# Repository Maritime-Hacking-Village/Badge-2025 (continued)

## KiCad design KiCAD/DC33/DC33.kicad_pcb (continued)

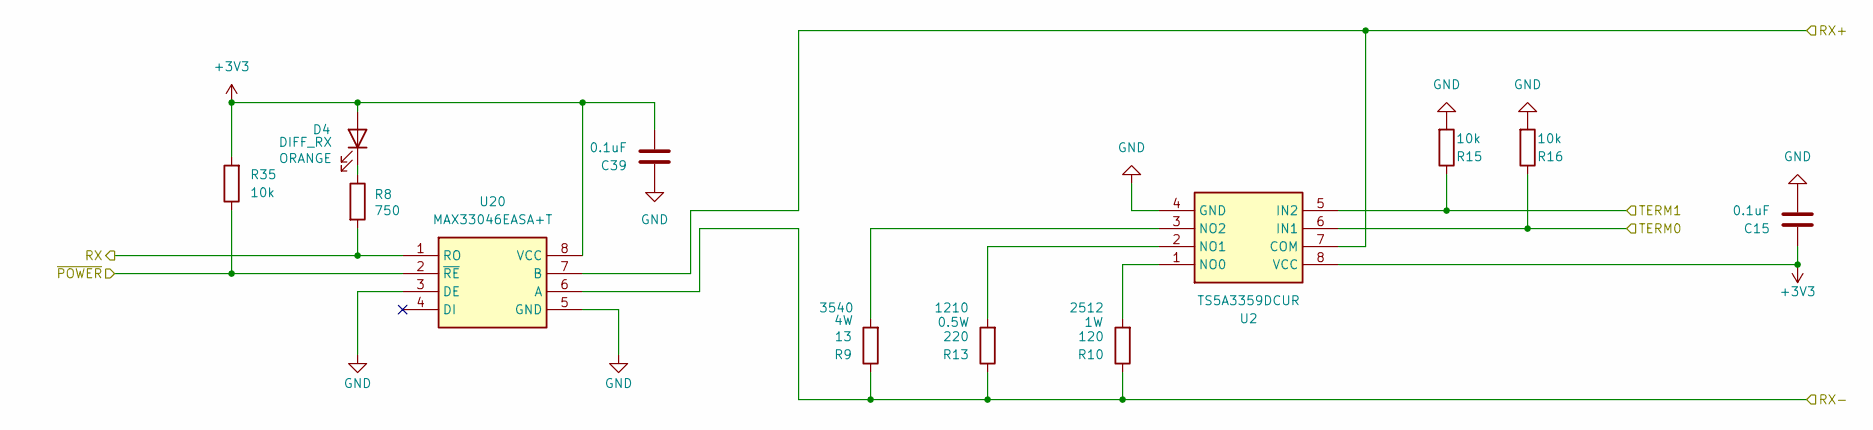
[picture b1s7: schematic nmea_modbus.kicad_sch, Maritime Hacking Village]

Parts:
C15, C39: 0.1uF; C_0603_1608Metric; Manufacturer Part Number KGM15BR71E104KT
D4: 1.8V/2MA ORANGE; LED_0603_1608Metric; Manufacturer Part Number APT1608LSECK/J4-PRV
R8: 750; R_0603_1608Metric; Tolerance 1%; Manufacturer Part Number ERJ-3EKF7500V
R9: 13; RES_3540; Tolerance 1%; Manufacturer Part Number 354013RFT
R10: 120; R_2512_6332Metric; Tolerance 1%; Manufacturer Part Number RC2512FK-07120RL
R13: 220; R_1210_3225Metric; Tolerance 1%; Manufacturer Part Number RC1210FR-07220RL
R15, R16, R35: 10k; R_0603_1608Metric; Tolerance 1%; Manufacturer Part Number CRG0603F10K
U2: TS5A3359DCUR; SOP50P310X90-8N; Manufacturer Part Number TS5A3359DCUR
U20: MAX33046EASA+T; SOIC127P600X175-8N; Manufacturer Part Number MAX33046EASA+T

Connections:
+3V3: C15.1, C39.2, D4.2 (A), R35.2, U2.8 (VCC), U20.8 (VCC); also elsewhere on the board
/Diff receiver/RX+: U2.7 (COM), U20.7 (B); also elsewhere on the board
/Diff receiver/RX-: R9.1, R10.1, R13.1, U20.6 (A); also elsewhere on the board
/PWR_RECEIVER: R35.1, U20.2 (~RE); also elsewhere on the board
/RX_TERM_SEL0: R16.1, U2.6 (IN1); also elsewhere on the board
/RX_TERM_SEL1: R15.1, U2.5 (IN2); also elsewhere on the board
/UART1_RX: R8.2, U20.1 (RO); also elsewhere on the board
GND: C15.2, C39.1, R15.2, R16.2, U2.4 (GND), U20.3 (DE), U20.5 (GND); also elsewhere on the board
unnamed: D4.1 (K), R8.1
unnamed: R10.2, U2.1 (NO0)
unnamed: R13.2, U2.2 (NO1)
unnamed: R9.2, U2.3 (NO2)

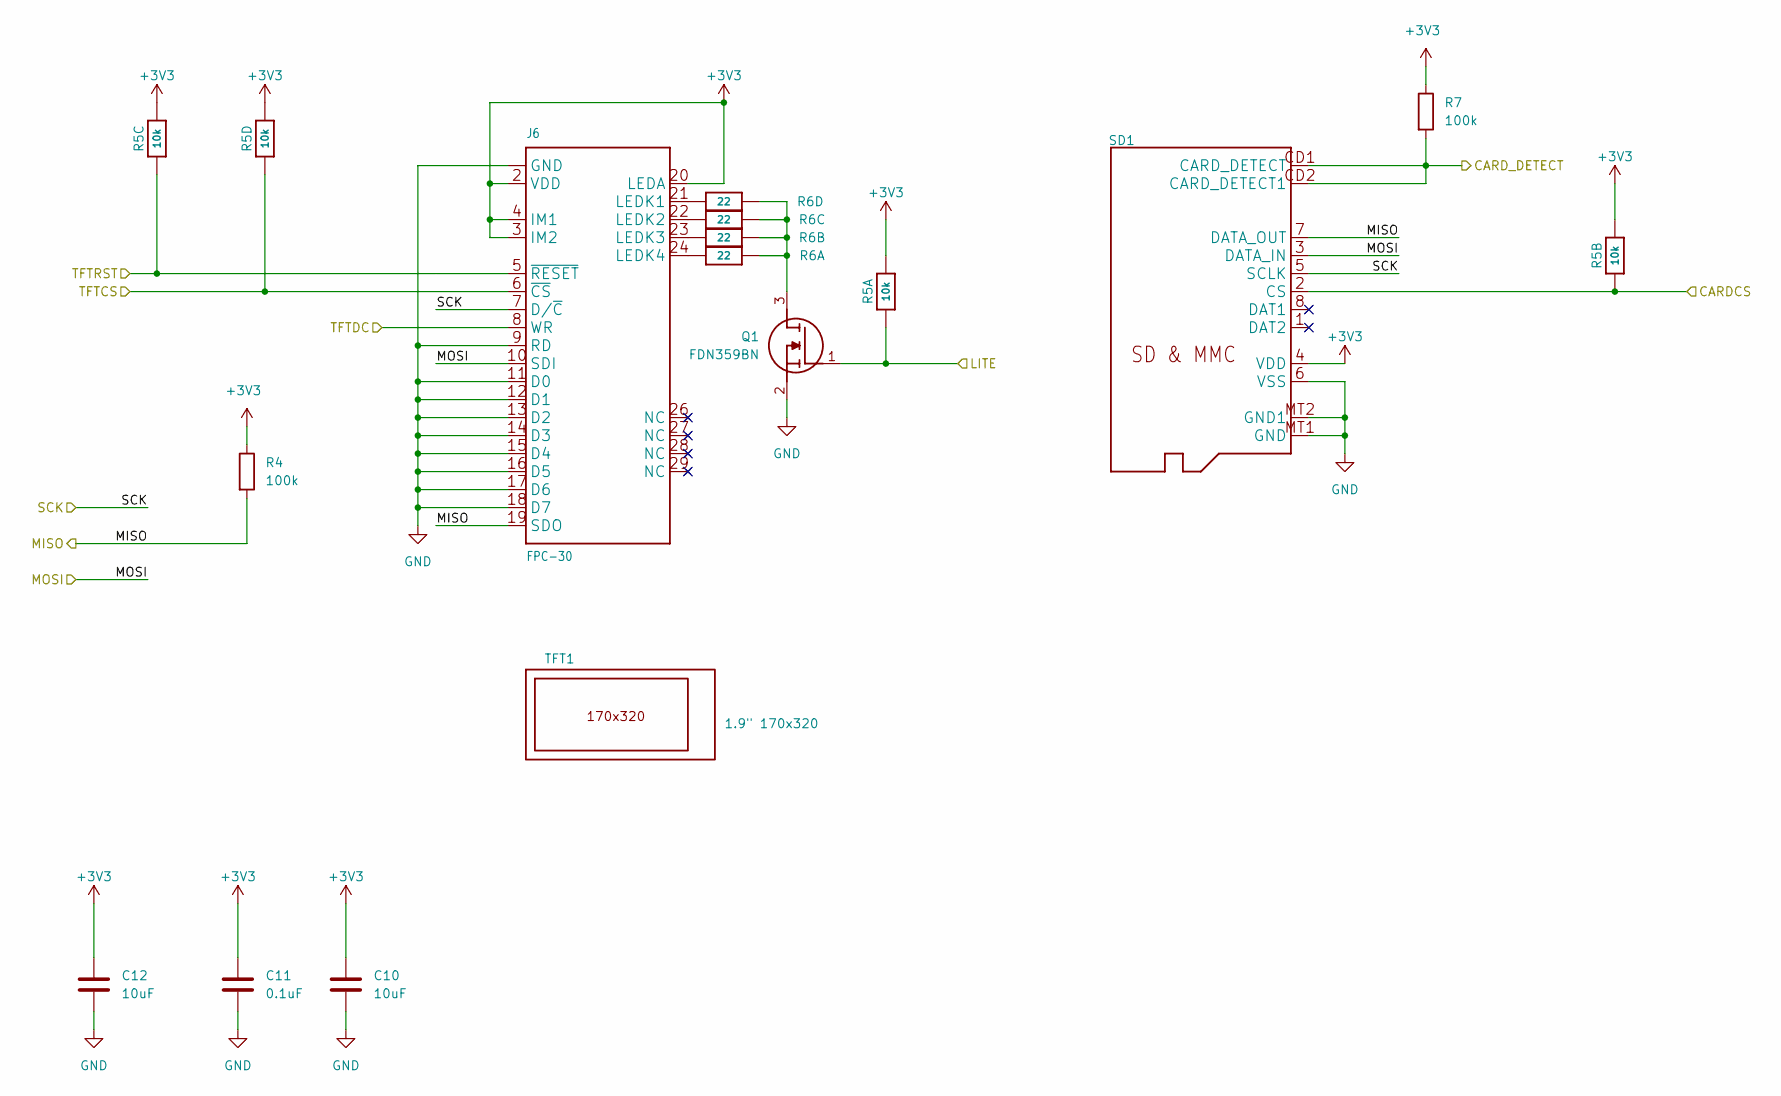
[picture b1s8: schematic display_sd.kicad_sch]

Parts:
C10, C12: 10uF; C_0603_1608Metric; Manufacturer Part Number GRM188R61E106MA73J
C11: 0.1uF; C_0603_1608Metric; Manufacturer Part Number KGM15BR71E104KT
J6: FPC-30; CON_541043031_MOL; Manufacturer Part Number 0541043031
Q1: FDN359BN; SOT95P251X112-3N; Manufacturer Part Number FDN359BN
R4, R7: 100k; R_0603_1608Metric; Tolerance 1%; Manufacturer Part Number ERJ-3EKF1003V
R5: 10k; RESPACK_4X0603; Tolerance 1%; Manufacturer Part Number EXB-38V103JV
R6: 22; RESPACK_4X0603; Tolerance 1%; Manufacturer Part Number EXB-38V220JV
SD1: MICROSD; Manufacturer Part Number 2908-05WB-MG
TFT1: 1.9" 170x320; TFT_1.9IN_170X320_30P; Manufacturer Part Number T190X7-C30-01

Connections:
+3V3: C10.1, C11.1, C12.1, J6.2 (VDD), J6.3 (IM2), J6.4 (IM1), J6.20 (LEDA), R4.1, R5.5 (2), R5.6 (2), R5.7 (2), R5.8 (2), R7.1, SD1.4 (VDD); also elsewhere on the board
/DISP_BACKLIGHT: Q1.1 (G), R5.1; also elsewhere on the board
/DISP_DC: J6.8 (WR); also elsewhere on the board
/DISP_RESET: J6.5 (~RESET), R5.3 (1); also elsewhere on the board
/SD_CD: R7.2, SD1.CD1 (CARD_DETECT), SD1.CD2 (CARD_DETECT1); also elsewhere on the board
/SD_CS: R5.2 (1), SD1.2 (CS); also elsewhere on the board
/SPI0_CS: J6.6 (~CS), R5.4 (1); also elsewhere on the board
/SPI0_RX: J6.19 (SDO), R4.2, SD1.7 (DATA_OUT); also elsewhere on the board
/SPI0_SCK: J6.7 (D/~C), SD1.5 (SCLK); also elsewhere on the board
/SPI0_TX: J6.10 (SDI), SD1.3 (DATA_IN); also elsewhere on the board
GND: C10.2, C11.2, C12.2, J6.1 (GND), J6.9 (RD), J6.11 (D0), J6.12 (D1), J6.13 (D2), J6.14 (D3), J6.15 (D4), J6.16 (D5), J6.17 (D6), J6.18 (D7), J6.25 (GND), J6.30 (GND), J6.MNT1 (GND), J6.MNT2 (GND), Q1.2 (S), SD1.6 (VSS), SD1.MT1 (GND), SD1.MT2 (GND1); also elsewhere on the board
unnamed: J6.21 (LEDK1), R6.4 (1)
unnamed: J6.22 (LEDK2), R6.3 (1)
unnamed: J6.23 (LEDK3), R6.2 (1)
unnamed: J6.24 (LEDK4), R6.1
unnamed: Q1.3 (D), R6.5 (2), R6.6 (2), R6.7 (2), R6.8 (2)

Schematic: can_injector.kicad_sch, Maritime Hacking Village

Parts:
C33, C36, C56: 0.1uF; C_0603_1608Metric; Manufacturer Part Number KGM15BR71E104KT
C44, C45: 0.1uF; C_0603_1608Metric; Manufacturer Part Number KGM15BR71E104KT; not fitted
C46, C47, C48, C57: 1uF; C_0603_1608Metric; Manufacturer Part Number CC0603KRX7R9BB105
R18: 10k; RESPACK_4X0603; Tolerance 1%; Manufacturer Part Number EXB-38V103JV
R19, R22, R45, R46, R49, R50, R53, R55: 2k; R_0603_1608Metric; Tolerance 0.1%; Manufacturer Part Number ERA-3AEB202V
R23: 10k; R_0603_1608Metric; Tolerance 1%; Manufacturer Part Number RC0603FR-0751KL
R38, R40: 13; RES_3540; Tolerance 1%; Manufacturer Part Number 354013RFT
R39, R41: 51k; R_0603_1608Metric; Tolerance 1%; Manufacturer Part Number RC0603FR-0751KL
R42, R51: 10k; R_0603_1608Metric; Tolerance 1%; Manufacturer Part Number CRG0603F10K
R44, R47, R48, R52, R54, R64: 1k; R_0603_1608Metric; Tolerance 0.1%; Manufacturer Part Number ERA-3AEB102V
R56, R57: 2.2k; R_0603_1608Metric; Tolerance 0.1%; Manufacturer Part Number ERA-3AEB102V
U17, U19: ADG849YKSZ-REEL; SOT65P210X110-6N; Manufacturer Part Number ADG849YKSZ-REEL
U21: ALM2403QPWPRQ1; ALM2403QPWPRQ1_TEX; Manufacturer Part Number ALM2403QPWPRQ1
U27: TPS22810TDBVRQ1; SOT95P280X145-6N; Manufacturer Part Number TPS22810TDBVRQ1

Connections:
+3V3: R42.2; also elsewhere on the board
+5V: C57.1, U27.1 (VIN); also elsewhere on the board
/Diff injector/+5V_SW: C33.1, C36.1, C46.1, C47.1, C48.1, C56.1, U17.2 (VDD), U19.2 (VDD), U21.10 (VS+), U21.11 (VS+), U21.12 (VS+), U27.5 (QOD), U27.6 (VOUT)
/Diff injector/H_V0: R50.2; also elsewhere on the board
/Diff injector/H_V1: R53.2; also elsewhere on the board
/Diff injector/H_V2: R55.2; also elsewhere on the board
/Diff injector/H_Z0: R18.8 (2), U19.1 (IN); also elsewhere on the board
/Diff injector/Injector Disconnect/COM0: U19.5 (D); also elsewhere on the board
/Diff injector/Injector Disconnect/COM1: U17.5 (D); also elsewhere on the board
/Diff injector/L_V0: R22.2; also elsewhere on the board
/Diff injector/L_V1: R45.2; also elsewhere on the board
/Diff injector/L_V2: R46.2; also elsewhere on the board
/Diff injector/L_Z0: R23.1, U17.1 (IN); also elsewhere on the board
/PWR_INJECTOR: R51.2, U27.3 (EN/UVLO); also elsewhere on the board
/TX_DISABLE: R42.1, U21.3 (OTF/SH_DN); also elsewhere on the board
GND: C33.2, C36.2, C44.1, C45.2, C46.2, C47.2, C48.2, C56.2, C57.2, R18.1, R19.2, R23.2, R49.2, R51.1, R56.1, R57.1, U17.3 (GND), U19.3 (GND), U21.6 (VS-), U21.14 (VS-), U21.EP (EPAD), U27.2 (GND); also elsewhere on the board
unnamed: R19.1, R22.1, R47.1
unnamed: R45.1, R47.2, R48.1
unnamed: R49.1, R50.1, R52.1
unnamed: R52.2, R53.1, R54.1
unnamed: R40.2, U17.4 (S1)
unnamed: R39.1, U17.6 (S2)
unnamed: R38.2, U19.4 (S1)
unnamed: R41.1, U19.6 (S2)
unnamed: R54.2, R55.1, U21.2 (IN(1)+)
unnamed: R57.2, R64.1, U21.1 (IN(1)-)
unnamed: R46.1, R48.2, U21.4 (IN(2)+)
unnamed: R44.2, U21.5 (IN(2)-)
unnamed: C44.2, R38.1, R41.2, R64.2, U21.13 (OUT(1))
unnamed: C45.1, R39.2, R40.1, R44.1, R56.2, U21.9 (OUT(2))

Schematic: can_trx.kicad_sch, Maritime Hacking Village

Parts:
C34, C64: 22pF; C_0603_1608Metric; Manufacturer Part Number CC0603JPNPO9BN220
C35, C40, C43, C63: 0.1uF; C_0603_1608Metric; Manufacturer Part Number KGM15BR71E104KT
C65: 1uF; C_0603_1608Metric; Manufacturer Part Number CC0603KRX7R9BB105
D2: 2.64V/2MA GREEN; LED_0603_1608Metric; Manufacturer Part Number APT1608LZGCK
D3: 1.8V/2MA ORANGE; LED_0603_1608Metric; Manufacturer Part Number APT1608LSECK/J4-PRV
R37: 750; R_0603_1608Metric; Tolerance 1%; Manufacturer Part Number ERJ-3EKF7500V
R60: 330; R_0603_1608Metric; Tolerance 1%; Manufacturer Part Number ERJ-3EKF3300V
R63: 10k; R_0603_1608Metric; Tolerance 1%; Manufacturer Part Number CRG0603F10K
U13: MCP2558FD-H_SN; SOIC127P600X175-8N; Manufacturer Part Number MCP2558FD-H/SN
U30: TPS22810TDBVRQ1; SOT95P280X145-6N; Manufacturer Part Number TPS22810TDBVRQ1
U31: MCP2518FD; SOIC-14_3.9x8.7mm_P1.27mm; Manufacturer Part Number MCP2518FDT-E/SL
Y1: 20MHz 18pF; Crystal_SMD_3225-4Pin_3.2x2.5mm; Manufacturer Part Number ECS-200-18-33-JGN-TR

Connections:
+3V3: C40.2, C43.1, D2.2 (A), D3.2 (A), U13.5 (VIO), U31.14 (VDD); also elsewhere on the board
+5V: C65.1, U30.1 (VIN); also elsewhere on the board
/CAN transceiver/+5V_SW: C35.1, C63.1, U13.3 (VDD), U30.5 (QOD), U30.6 (VOUT)
/CAN transceiver/CAN TRX Disconnect/COM0: U13.6 (CANL); also elsewhere on the board
/CAN transceiver/CAN TRX Disconnect/COM1: U13.7 (CANH); also elsewhere on the board
/CAN transceiver/INT: U31.4 (~INT); also elsewhere on the board
/CAN transceiver/SOF: U31.3 (CLKO/SOF); also elsewhere on the board
/PWR_TRX: R63.2, U30.3 (EN/UVLO); also elsewhere on the board
/SAO_GPIO2: U31.8 (~INT1/GPIO1); also elsewhere on the board
/SPI1_CSn: U31.13 (nCS); also elsewhere on the board
/SPI1_RX: U31.12 (SDO); also elsewhere on the board
/SPI1_SCK: U31.10 (SCK); also elsewhere on the board
/SPI1_TX: U31.11 (SDI); also elsewhere on the board
GND: C34.2, C35.2, C40.1, C43.2, C63.2, C64.2, C65.2, R63.1, U13.2 (VSS), U30.2 (GND), U31.7 (VSS), Y1.2, Y1.4; also elsewhere on the board
unnamed: D2.1 (K), R60.1
unnamed: D3.1 (K), R37.1
unnamed: R60.2, U13.4 (RXD), U31.2 (RXCAN)
unnamed: U13.8 (S), U31.9 (~INT0/GPIO0/XSTBY)
unnamed: R37.2, U13.1 (TXD), U31.1 (TXCAN)
unnamed: C64.1, U31.6 (OSC1), Y1.1
unnamed: C34.1, U31.5 (OSC2), Y1.3

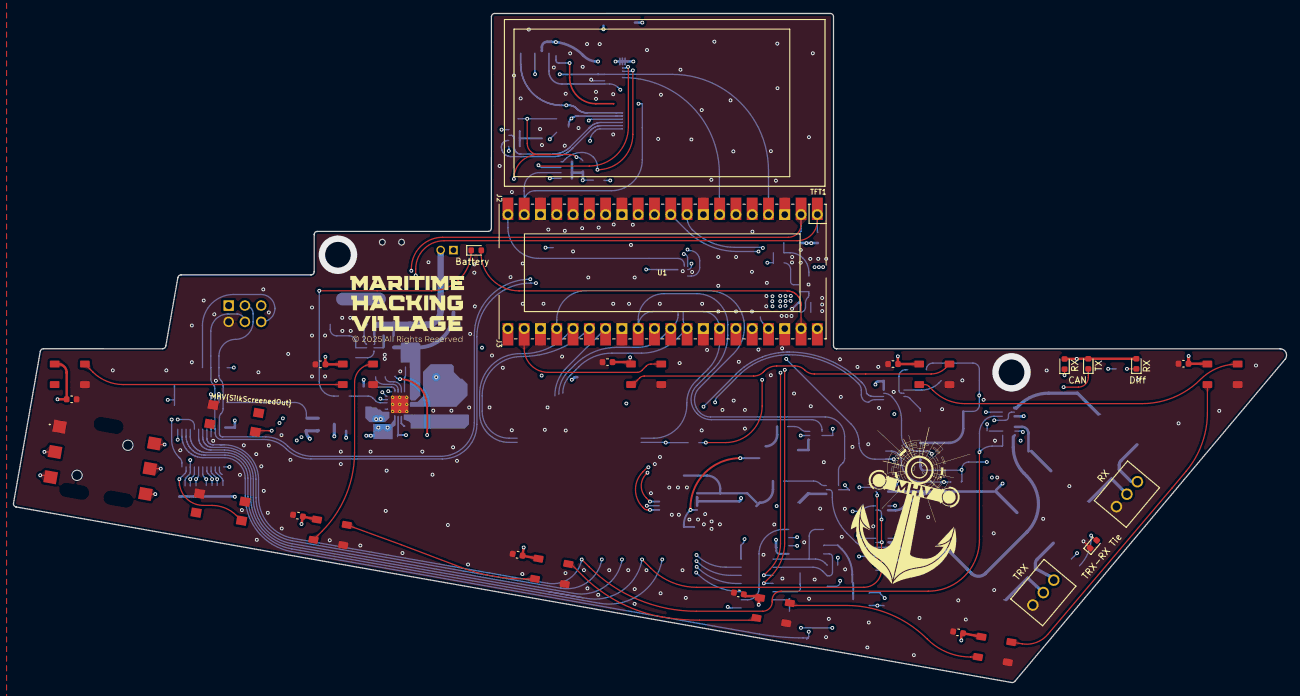
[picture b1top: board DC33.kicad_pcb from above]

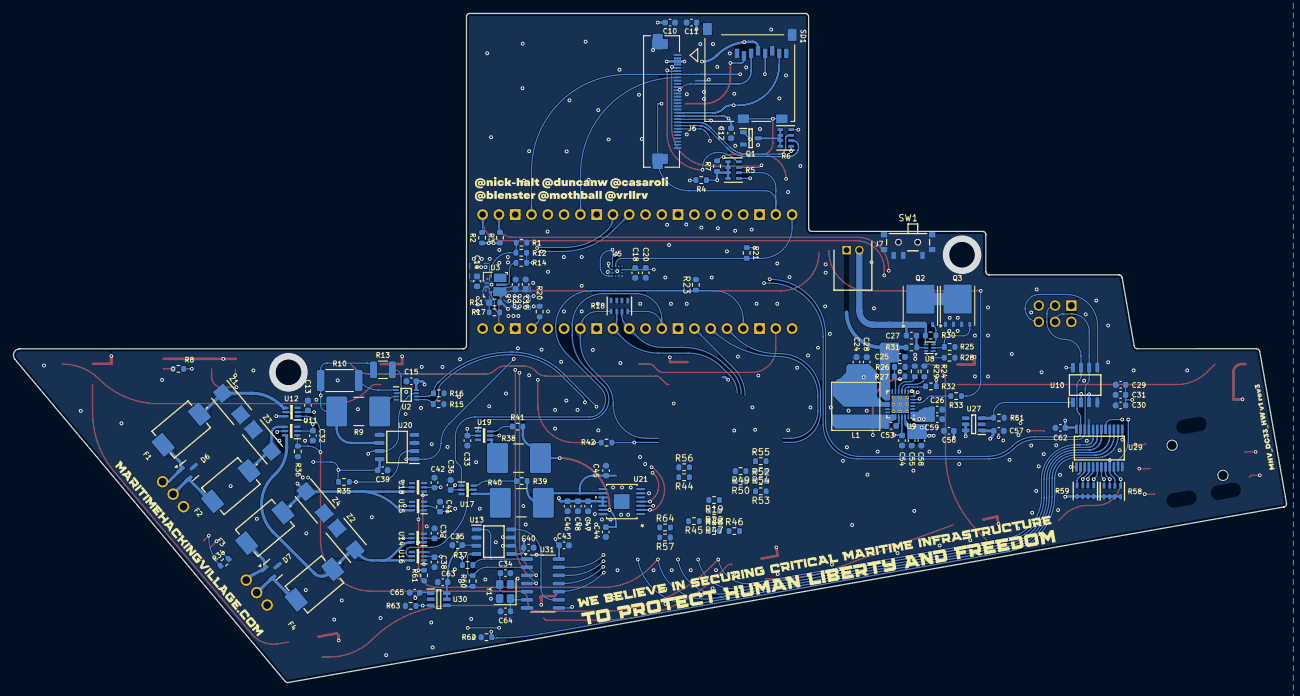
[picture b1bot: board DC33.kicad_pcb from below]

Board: 4 copper layers, 198.5 x 104.3 mm, 182 parts (149 on the bottom side), 127 nets.

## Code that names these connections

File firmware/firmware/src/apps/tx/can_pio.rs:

//! Pio backed uart drivers

use embassy_rp::{
    clocks::clk_sys_freq,
    pio::{
        Common, Config, Direction, Instance, LoadedProgram, PioPin, ShiftDirection, StateMachine,
    },
    Peri,
};
use fixed::{traits::ToFixed, types::extra::U8, FixedU32};

use crate::apps::tx::TxError;

/// This struct represents a uart tx program loaded into pio instruction memory.
pub struct PioCanTrxProgram<'d, PIO: Instance> {
    prg: LoadedProgram<'d, PIO>,
}

impl<'d, PIO: Instance> PioCanTrxProgram<'d, PIO> {
    /// Load the uart tx program into the given pio
    pub fn new(common: &mut Common<'d, PIO>) -> Self {
        // let prg = pio::pio_asm!(
        //     r#"
        //     .define DOMINANT 0b010
        //     .define RECESSIVE 0b101

        //     wait_ifs:
        //         set pins, RECESSIVE         ; OUTPUT recessive
        //     ifs_loop_reset:
        //         set x, 0b11                 ; we need 3 recessive bits before we start
        //         mov isr, x                  ; 7 bits * 16 (oversample) / 2 (instructions) = 24 = 0x18
        //         in null, 3                  ; shift left 3
        //     ifs_loop:
        //         jmp x-- idle                ; got ifs, jump to idle
        //         jmp pin ifs_loop            ; recessive just keep counting
        //         jmp ifs_loop_reset          ; got dominant, reset counter
        //     idle:
        //         jmp !osre tx_bit
        //     eof:
        //         irq 0 [1]                   ; IRQ0 = EOF
        //         set pins, RECESSIVE         ; OUTPUT recessive
        //         set x, 7                    ; eof is recessive for 7 bits
        //     eof_loop:
        //         jmp x-- eof_loop [15]
        //         jmp wait_ifs
        //     tx_bit:
        //         out x, 1                    ; get next bit
        //         jmp !x dominant
        //     recessive:
        //         set pins, RECESSIVE [7]     ; OUTPUT recessive
        //         jmp pin idle [3]            ; check for recessive
        //         irq 1                       ; IRQ1 = arbitration error
        //         jmp wait_ifs                ; reset
        //     dominant:
        //         set pins, DOMINANT [7]      ; OUTPUT dominant
        //         jmp idle [3]
        // "#
        // );
        let prg = pio::pio_asm!(
            r#"
            .side_set 3 opt
            .define DOMINANT         0b00100
            .define RECESSIVE        0b10011
            .define STRONG_RECESSIVE 0b00010
            .define SIDE_RECESSIVE   0b001
            .define SIDE_DOMINANT    0b011

            ; initialize x to be 0xffffffff
            mov x, ! null

            loop:
                jmp !osre prepare
                pull noblock
            inner:
                out y, 1
                jmp !y dominant
            recessive:
                set pins RECESSIVE side SIDE_RECESSIVE
                jmp loop
            dominant:
                set pins DOMINANT side SIDE_DOMINANT
                jmp loop
            prepare:
                jmp inner
        "#
        );
        let prg = common.load_program(&prg.program);

        Self { prg }
    }
}

/// PIO backed Uart transmitter
pub struct PioCanTrx<'d, PIO: Instance, const SM: usize> {
    sm: StateMachine<'d, PIO, SM>,
}

impl<'d, PIO: Instance, const SM: usize> PioCanTrx<'d, PIO, SM> {
    /// Configure a pio state machine to use the loaded tx program.
    pub fn new(
        baud: u32,
        common: &mut Common<'d, PIO>,
        mut sm: StateMachine<'d, PIO, SM>,
        l_z0: Peri<'d, impl PioPin>,
        l_v2: Peri<'d, impl PioPin>,
        l_v1: Peri<'d, impl PioPin>,
        l_v0: Peri<'d, impl PioPin>,
        h_z0: Peri<'d, impl PioPin>,
        h_v2: Peri<'d, impl PioPin>,
        h_v1: Peri<'d, impl PioPin>,
        h_v0: Peri<'d, impl PioPin>,
        program: &PioCanTrxProgram<'d, PIO>,
    ) -> Result<Self, TxError> {
        let l_z0 = common.make_pio_pin(l_z0);
        let l_v2 = common.make_pio_pin(l_v2);
        let l_v1 = common.make_pio_pin(l_v1);
        let l_v0 = common.make_pio_pin(l_v0);
        let h_z0 = common.make_pio_pin(h_z0);
        let h_v2 = common.make_pio_pin(h_v2);
        let h_v1 = common.make_pio_pin(h_v1);
        let h_v0 = common.make_pio_pin(h_v0);
        sm.set_pin_dirs(
            Direction::Out,
            &[&l_z0, &l_v2, &l_v1, &l_v0, &h_z0, &h_v2, &h_v1, &h_v0],
        );

        let mut cfg = Config::default();
        cfg.set_set_pins(&[&l_z0, &l_v2, &l_v1, &l_v0, &h_z0]);
        cfg.use_program(&program.prg, &[&h_v2, &h_v1, &h_v0]);
        cfg.shift_out.direction = ShiftDirection::Left;
        cfg.clock_divider = Self::clk_div(baud)?;
        sm.set_config(&cfg);

        Ok(Self { sm })
    }

    pub fn clk_div(baud: u32) -> Result<FixedU32<U8>, TxError> {
        fn _check_clock_div(div: FixedU32<U8>) -> Result<(), TxError> {
            if div < FixedU32::<U8>::from_num(1.0) {
                Err(TxError::ClockDividerTooSmall)
            } else if div > FixedU32::<U8>::from_bits(0xFFFF_FF00) {
                Err(TxError::ClockDividerTooLarge)
            } else {
                Ok(())
            }
        }

        let divisor = 6_u32
            .checked_mul(baud)
            .ok_or(TxError::ClockDividerTooSmall)?;

        let clk_div = (clk_sys_freq() / divisor).to_fixed();
        _check_clock_div(clk_div)?;

        Ok(clk_div)
    }

    /// Modify the PIO baud.
    pub fn set_baud(&mut self, baud: u32) -> Result<(), TxError> {
        let clk_div = Self::clk_div(baud)?;
        let enabled = self.is_enabled();

        if enabled {
            self.disable()
        }

        self.sm.set_clock_divider(clk_div);

        if enabled {
            self.enable()
        }

        self.sm.clkdiv_restart();
        self.restart();

        Ok(())
    }

    pub fn is_enabled(&self) -> bool {
        self.sm.is_enabled()
    }

    /// Enable's the PIO program, continuing the wave generation from the PIO program.
    pub fn enable(&mut self) {
        self.sm.set_enable(true);
    }

    /// Stops the PIO program, ceasing all signals from the PIN that were generated via PIO.
    pub fn disable(&mut self) {
        self.sm.set_enable(false);
    }

    pub fn restart(&mut self) {
        self.sm.restart();
    }

    /// Write a single u8
    pub async fn write_word(&mut self, word: u32) {
        self.sm.tx().wait_push(word).await;
    }
}

// impl<PIO: Instance, const SM: usize> ErrorType for PioCanTrx<'_, PIO, SM> {
//     type Error = Infallible;
// }

// impl<PIO: Instance, const SM: usize> Write for PioCanTrx<'_, PIO, SM> {
//     async fn write(&mut self, buf: &[u8]) -> Result<usize, Infallible> {
//         for byte in buf {
//             self.write_u8(*byte).await;
//         }
//         Ok(buf.len())
//     }
// }

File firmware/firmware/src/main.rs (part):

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    let mut joy_left = gpio_exp_1_pins.remove(0);
    let mut button_a = gpio_exp_1_pins.remove(0);
    let mut button_b = gpio_exp_1_pins.remove(0);
    let disp_reset = gpio_exp_1_pins.remove(0);
    let sao_gpio_1 = gpio_exp_1_pins.remove(0);
    let tx_connect = gpio_exp_1_pins.remove(0);
    let tx_enable = gpio_exp_1_pins.remove(0);
    let mut _can_disconnect = gpio_exp_1_pins.remove(0);
    let mut _sd_cd = gpio_exp_1_pins.remove(0);
    let term_sel0 = gpio_exp_1_pins.remove(0);
    let term_sel1 = gpio_exp_1_pins.remove(0);
    let tx_rx_tie = gpio_exp_1_pins.remove(0);
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    let (gpio_exp_2_ctrl, _, gpio_exp_2_pins) = i2c_io_expander::setup::<_, _, PCA9536, 4>(i2c_bus);
    let mut gpio_exp_2_pins = Vec::from(gpio_exp_2_pins);

    let pwr_injector = gpio_exp_2_pins.remove(0);
    let mut _pwr_trx = gpio_exp_2_pins.remove(0);
    let mut pwr_receiver = gpio_exp_2_pins.remove(0);
    let sao_gpio_2 = gpio_exp_2_pins.remove(0);

    // Battery charger (BQ25895)
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
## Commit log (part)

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2025-07-31 init
2025-07-31 firmware dir
2025-08-02 add flag
2025-08-02 remove flag
2025-08-05 contrib
2025-08-05 dazzle scripts
2025-08-05 license
2025-08-05 firmware map
2025-08-05 stuff
2025-08-08 docs
2025-08-08 top-level readme
2025-08-08 move readme
2025-08-08 another example
2025-08-09 fix md formatting
2025-08-12 firmware release
2025-08-13 tweaks to readme
2025-08-15 missing content
2025-08-15 extra file
2025-08-15 minor typo
2025-08-15 fix flash script
2025-08-15 licenses
2025-08-15 oops fix license
2025-08-15 remove dead README
2025-08-20 readme tweak
2025-08-20 readme
2025-08-28 missing cargo config
